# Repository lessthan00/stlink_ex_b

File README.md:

# stlink_ex_b

stlink_ex_b: 修改了板子的形状, 2x7 2x5 改为简易牛角接口, 丝印改到正确的位置

stlink_ex_a: JTGA 和SWD1.27mm间距和2.54mm间距

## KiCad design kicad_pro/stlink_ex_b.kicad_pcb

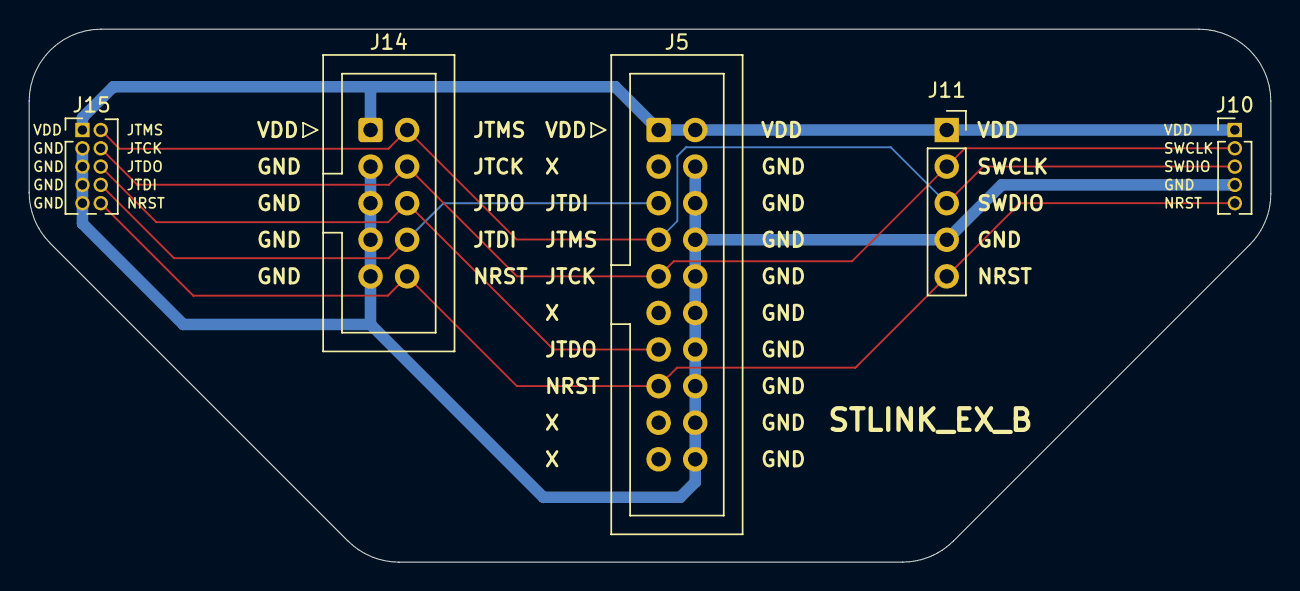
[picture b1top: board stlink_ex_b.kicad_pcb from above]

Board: 2 copper layers, 86.2 x 37.0 mm, 5 parts (0 on the bottom side), 7 nets.

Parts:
J5: Conn_02x10_Odd_Even; IDC-Header_2x10_P2.54mm_Vertical
J10: PINHD_1x5_Female; PinHeader_1x05_P1.27mm_Vertical
J11: PINHD_1x5_Female; PinSocket_1x05_P2.54mm_Vertical
J14: Conn_02x05_Odd_Even; IDC-Header_2x05_P2.54mm_Vertical
J15: Conn_02x05_Odd_Even; PinHeader_2x05_P1.27mm_Vertical

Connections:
/GND: J5.4, J5.6, J5.8, J5.10, J5.12, J5.14, J5.16, J5.18, J5.20, J10.4, J11.4, J14.3, J14.5, J14.7, J14.9, J15.3, J15.5, J15.7, J15.9
/JTCK: J5.9, J10.2, J11.2, J14.4, J15.4
/JTDI: J5.5, J14.8, J15.8
/JTDO: J5.13, J14.6, J15.6
/JTMS: J5.7, J10.3, J11.3, J14.2, J15.2
/MCU VDD: J5.1, J5.2, J10.1, J11.1, J14.1, J15.1
/NRST: J5.15, J10.5, J11.5, J14.10, J15.10
